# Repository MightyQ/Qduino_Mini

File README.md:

The Qduino Mini is *perfect* to embed in your electronics projects, it's super small, inexpensive, has a battery connector & charger built-in, & a fuel gauge that can tell you when to charge the battery!

The **Qduino Mini is Arduino-compatible & 100% open source, hardware and software** meaning that making and programming your first circuit is a breeze.  Hardware is hard, so we decided to make it a little bit easier.  All of the design files, including EAGLE board files, schematic, and code have been released under an open source license.  Here's what it includes:

* **Battery Charger Circuit** - just plug in USB and it charges the battery with the auto switching circuit - there's no extra charger needed & no digging the battery out of your project so you can charge & program at the same time over USB!
* **Battery Fuel Gauge** - guessing on when your project runs out of juice?  We've got you covered - we have a simple monitor library for your battery so you can remind yourself when it needs a little extra juice.
* **Ultra small, Ultra thin, Ultra light** - The Qduino Mini itself is 0.8in x 1.5in (2cm x 3.9cm) & 0.18oz (5 grams), perfect for quadcopters, drones or high altitude balloon projects.  Both the Qduino Mini and the batteries (LiPos) used to power the board fit are super compact & thin, just right for embedding in your projects.

######Tech Specs:

* **ATmega32U4 Processor** - Arduino Leonardo Compatible
* 32KB Flash Storage
* 2.5KB SRAM
* 1KB EEPROM
* 3.3V @ 8MHz
* 20 Digital I/O // 14 Dedicated
* 12 Analog Channels // 6 Dedicated
* 7 Digital I/O also PWM channels
* SPI, I2C, UART available
* Two RGB LEDs built-in - one for: Charge Status, TX, RX, and the * other user programmable
* **TPS78233** 3.3V 150mA Regulator
* **MCP73832** LiPo Battery Charger
* **MAX17048** LiPo Battery Fuel Gauge

The Qduino Mini is 100% made in the USA! Every board is made and quality tested at SparkFun Electronics, in Niwot, CO.

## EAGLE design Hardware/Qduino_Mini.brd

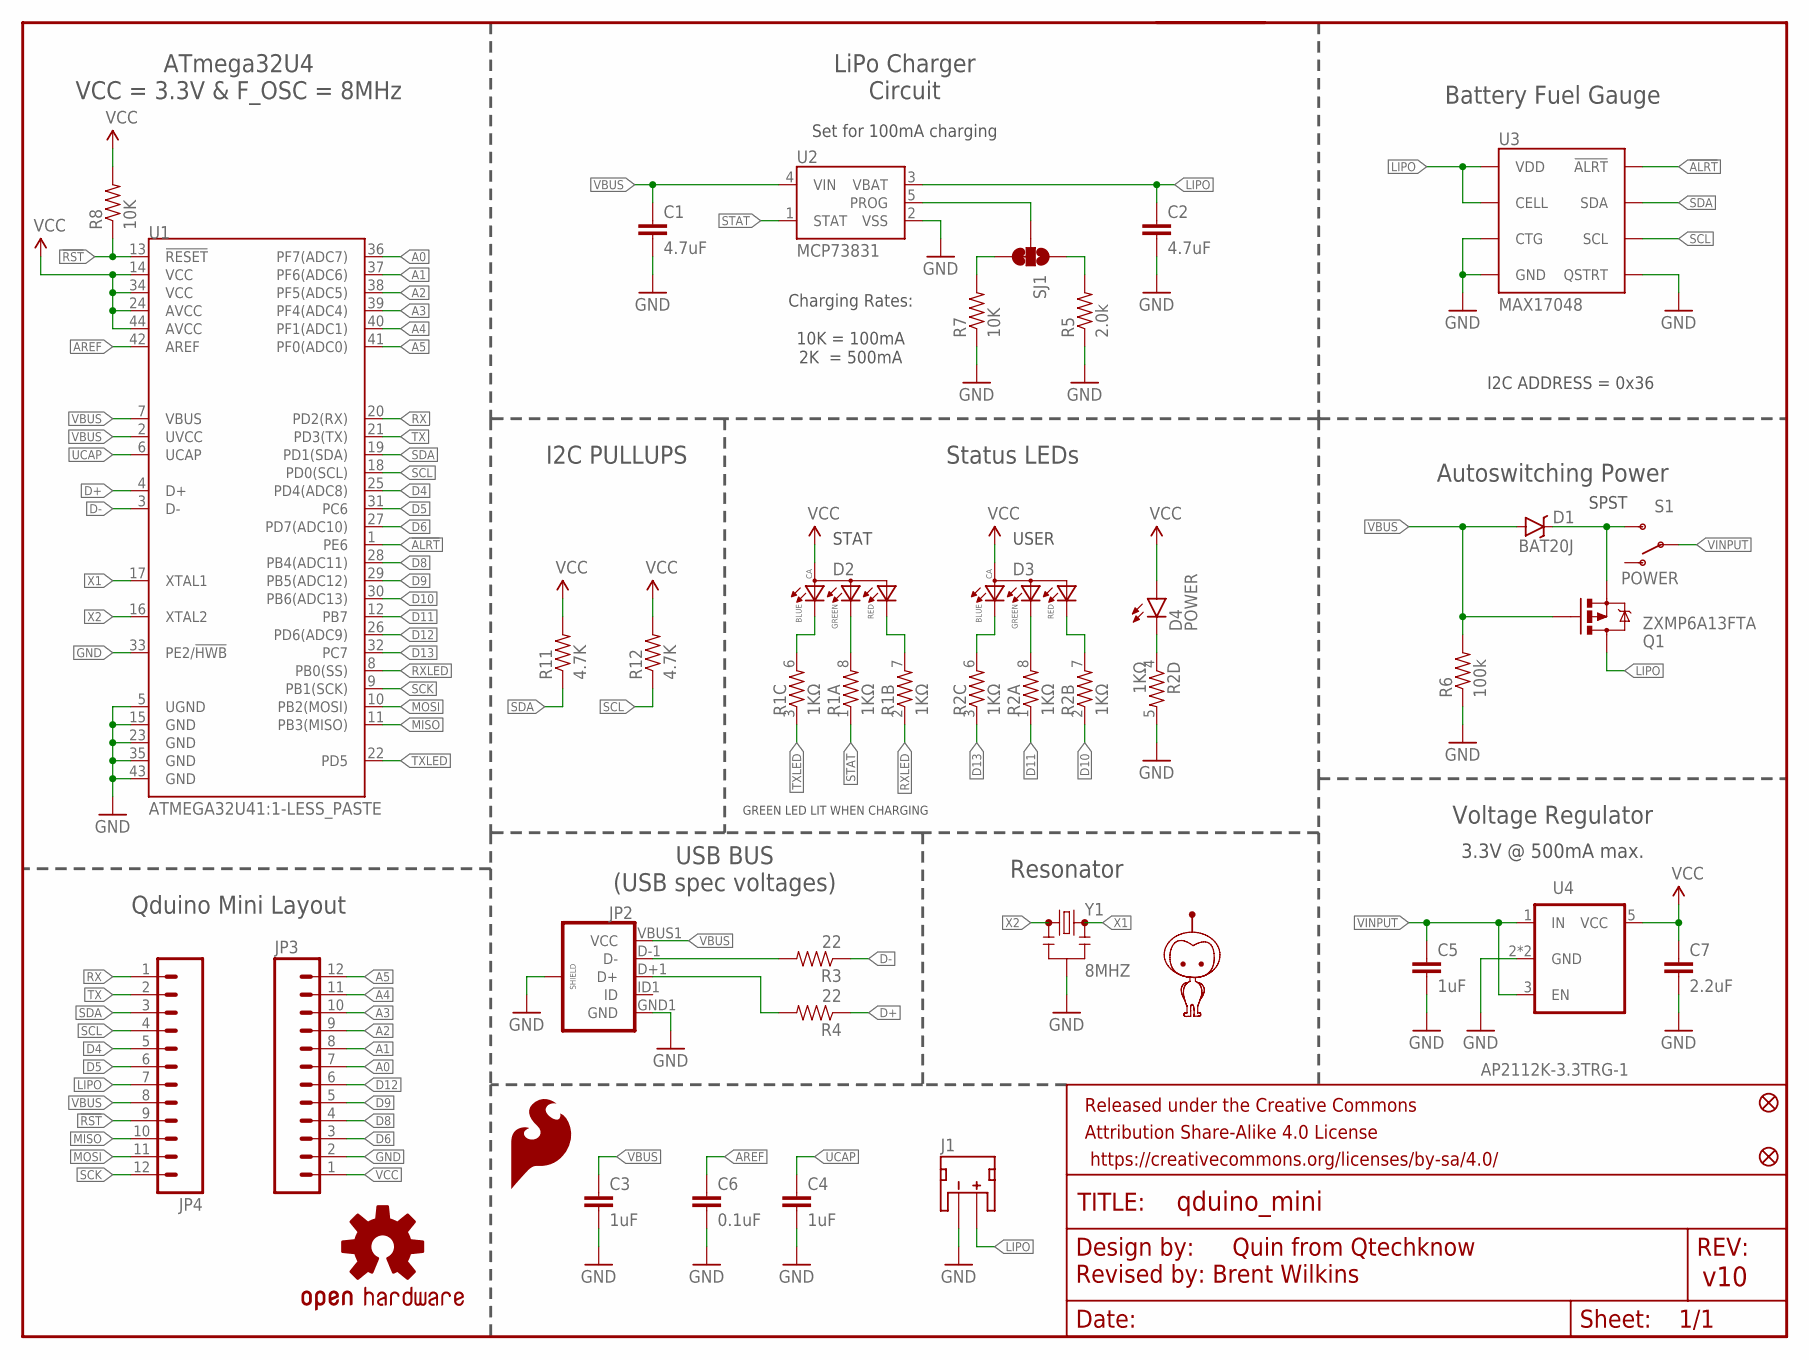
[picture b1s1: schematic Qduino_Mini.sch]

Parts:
C1, C2: 4.7uF; 0603-CAP
C3, C4, C5: 1uF; 0603-CAP
C6: 0.1uF; 0603-CAP
C7: 2.2uF; 0603-CAP
D1: BAT20J; SOD-323
D2, D3: 0.13_RGB_LEDPLCC; P-LCC-4-3
D4: POWER; LED-0603
FID1, FID2: FIDUCIALUFIDUCIAL; MICRO-FIDUCIAL
FRAME2: FRAME-LETTER; CREATIVE_COMMONS
J1: LiPo; JST-2-SMD
JP2: USB_MICROB_PLUGCONN-11752; USB-B-MICRO-SMD_V03
JP3, JP4: M12PTH; 1X12
LOGO1: OSHW-LOGOS; OSHW-LOGO-S
LOGO2: SFE_LOGO_FLAME.1_INCH; SFE_LOGO_FLAME_.1
Q1: ZXMP6A13FTA; SOT23-3
R1, R2: 1KΩ; 0603-ARV
R3, R4: 22; 0603-RES
R5: 2.0k; 0603-RES
R6: 100k; 0603-RES
R7, R8: 10K; 0603-RES
R11, R12: 4.7K; 0603-RES
S1: POWER; SWITCH-SPST-SMD-A
SJ1: JUMPER-PAD-3-2OF3_NC_BY_TRACE_SMALL; PAD-JUMPER-3-2OF3_NC_BY_TRACE_YES_SILK_FULL_BOX
U1: ATMEGA32U41:1-LESS_PASTE; QFN-44-NOPAD_1:1-LESS_PASTE
U2: MCP73831; SOT23-5
U3: MAX17048; DFN-8
U4: AP2112K-3.3TRG-1; SOT23-5
U5: MIGHTYQ-L-SILK; LOGO-LARGE-SILK
Y1: 8MHZ; RESONATOR-SMD

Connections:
!ALRT: U1.1 (PE6), U3.P$5 (!ALRT)
!RST: JP4.9, R8.1, U1.13 (!RESET)
A0: JP3.7, U1.36 (PF7(ADC7))
A1: JP3.8, U1.37 (PF6(ADC6))
A2: JP3.9, U1.38 (PF5(ADC5))
A3: JP3.10, U1.39 (PF4(ADC4))
A4: JP3.11, U1.40 (PF1(ADC1))
A5: JP3.12, U1.41 (PF0(ADC0))
AREF: C6.1, U1.42 (AREF)
D4: JP4.5, U1.25 (PD4(ADC8))
D5: JP4.6, U1.31 (PC6)
D6: JP3.3, U1.27 (PD7(ADC10))
D8: JP3.4, U1.28 (PB4(ADC11))
D9: JP3.5, U1.29 (PB5(ADC12))
D10: R2.2 (1), U1.30 (PB6(ADC13))
D11: R2.1, U1.12 (PB7)
D12: JP3.6, U1.26 (PD6(ADC9))
D13: R2.3 (1), U1.32 (PC7)
D+: R4.1, U1.4 (D+)
D-: R3.1, U1.3 (D-)
GND: C1.2, C2.2, C3.2, C4.2, C5.2, C6.2, C7.2, J1.1 (-), JP2.GND1 (GND), JP2.SHIELD1 (SHIELD), JP2.SHIELD2 (SHIELD), JP2.SHIELD3 (SHIELD), JP3.2, R2.5 (2), R5.1, R6.1, R7.1, U1.5 (UGND), U1.15 (GND), U1.23 (GND), U1.33 (PE2/!HWB), U1.35 (GND), U1.43 (GND), U2.2 (VSS), U3.P$1 (CTG), U3.P$4 (GND), U3.P$6 (QSTRT), U3.P$9 (GND), U4.2 (GND), U4.4 (GND), Y1.2
INMOSFET: D1.C, Q1.2 (S), S1.3 (S)
LIPO: C2.1, J1.2 (+), JP4.7, Q1.3 (D), U2.3 (VBAT), U3.P$2 (CELL), U3.P$3 (VDD)
MISO: JP4.10, U1.11 (PB3(MISO))
MOSI: JP4.11, U1.10 (PB2(MOSI))
unnamed: D2.3 (BLUE), R1.6 (2)
unnamed: D2.2 (GREEN), R1.8 (2)
unnamed: D3.3 (BLUE), R2.6 (2)
unnamed: D4.C, R2.4 (1)
unnamed: R7.2, SJ1.3
unnamed: R5.2, SJ1.1
unnamed: D3.2 (GREEN), R2.8 (2)
unnamed: D2.1 (RED), R1.7 (2)
unnamed: D3.1 (RED), R2.7 (2)
PROG: SJ1.2, U2.5 (PROG)
RX: JP4.1, U1.20 (PD2(RX))
RXLED: R1.2 (1), U1.8 (PB0(SS))
SCK: JP4.12, U1.9 (PB1(SCK))
SCL: JP4.4, R12.1, U1.18 (PD0(SCL)), U3.P$7 (SCL)
SDA: JP4.3, R11.1, U1.19 (PD1(SDA)), U3.P$8 (SDA)
STAT: R1.1, U2.1 (STAT)
TX: JP4.2, U1.21 (PD3(TX))
TXLED: R1.3 (1), U1.22 (PD5)
UCAP: C4.1, U1.6 (UCAP)
UD+: JP2.D+1 (D+), R4.2
UD-: JP2.D-1 (D-), R3.2
VBUS: C1.1, C3.1, D1.A, JP2.VBUS1 (VCC), JP4.8, Q1.1 (G), R6.2, U1.2 (UVCC), U1.7 (VBUS), U2.4 (VIN)
VCC: C7.1, D2.4 (ANODE), D3.4 (ANODE), D4.A, JP3.1, R8.2, R11.2, R12.2, U1.14 (VCC), U1.24 (AVCC), U1.34 (VCC), U1.44 (AVCC), U4.5 (VCC)
VINPUT: C5.1, S1.2, U4.1 (IN), U4.3 (EN)
X1: U1.17 (XTAL1), Y1.3
X2: U1.16 (XTAL2), Y1.1

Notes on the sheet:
Set for 100mA charging
USB BUS (USB spec voltages)
Resonator
Status LEDs
3.3V @ 500mA max.
SPST
ATmega32U4 VCC = 3.3V & F_OSC = 8MHz
Qduino Mini Layout
LiPo Charger Circuit
Battery Fuel Gauge
Voltage Regulator
Autoswitching Power
Charging Rates: 10K = 100mA 2K = 500mA
I2C PULLUPS
Revised by: Brent Wilkins
I2C ADDRESS = 0x36
USER
STAT
GREEN LED LIT WHEN CHARGING

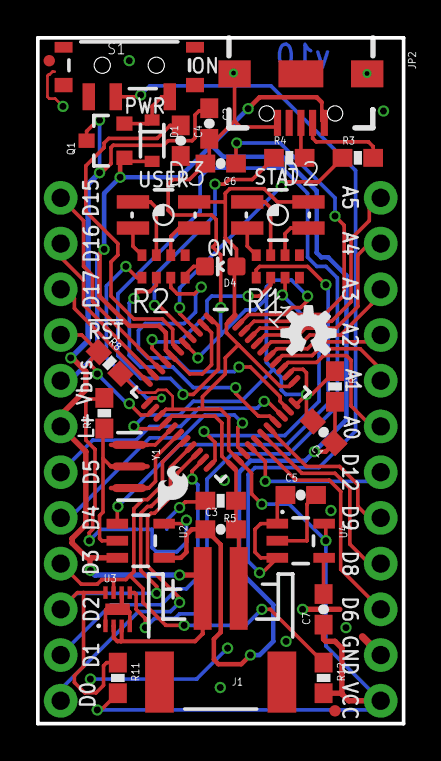
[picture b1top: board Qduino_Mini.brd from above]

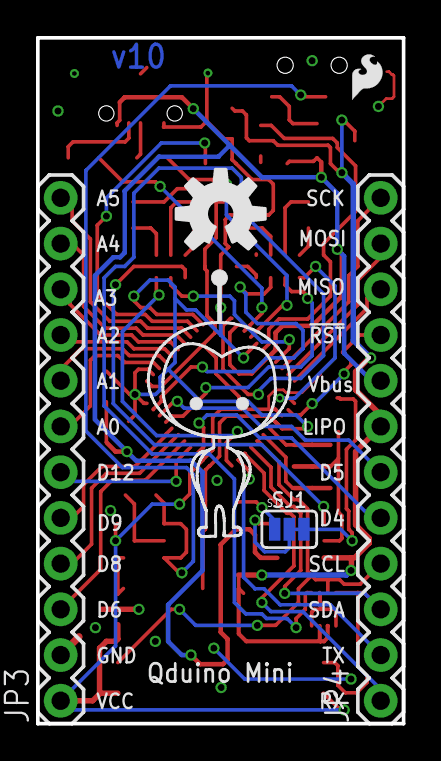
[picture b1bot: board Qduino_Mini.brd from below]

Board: 2 copper layers, 20.3 x 38.1 mm, 41 parts (6 on the bottom side), 51 nets.

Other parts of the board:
LOGO3: SFE_LOGO_FLAME.1_INCH; SFE_LOGO_FLAME_.1@1
U$4: OSHW-LOGO-M

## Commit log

2015-08-09 first commit - new read
2015-08-09 added software and V2 hardware
2015-08-11 Change RGB strings to enum Colors
2015-08-11 Update examples to work with Color enum
2015-08-11 updated to work w/ color enum, shrinked picture size
2015-08-11 updated data sheet for the correct part
2015-08-16 updated the zip file

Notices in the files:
parts and their libraries:
SparkFun-Passives: Licensing: CC v3.0 Share-Alike You are welcome to use this library for commercial purposes.
SparkFun-Aesthetics: Released under the Creative Commons Attribution Share-Alike 4.0 License
SparkFun-Aesthetics: https://creativecommons.org/licenses/by-sa/4.0
